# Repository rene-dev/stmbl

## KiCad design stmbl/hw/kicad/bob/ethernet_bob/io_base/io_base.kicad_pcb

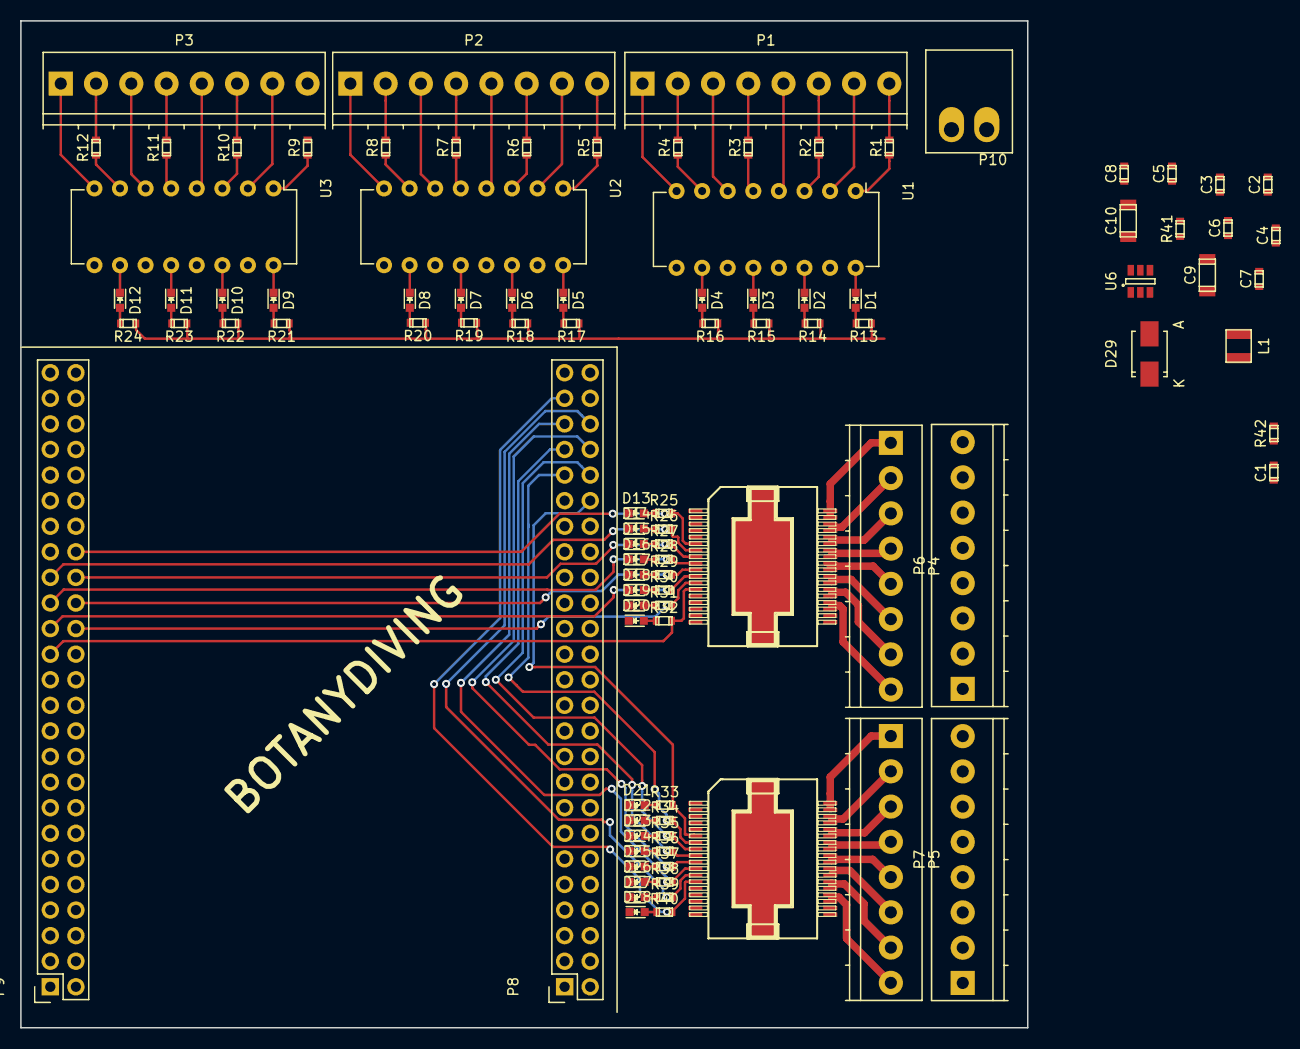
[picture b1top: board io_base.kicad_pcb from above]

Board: 2 copper layers, 99.9 x 99.9 mm, 98 parts (0 on the bottom side), 115 nets.

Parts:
C1, C2, C3, C4, C5, C6, C7, C8: 100n; C_0603
C9, C10: 10µ; C_1206
D1, D2, D3, D4, D5, D6, D7, D8, D9, D10, D11, D12, D13, D14, D15, D16, D17, D18, D19, D20, D21, D22, D23, D24, D25, D26, D27, D28: LED; LED_0603
D29: B240A; SMA_Standard
L1: 4.7µH 1.5A; SMD_INDUCTOR_32x25
P1, P2, P3, P4, P5, P6, P7: CONN_01X08; TerminalBlock_Pheonix_PT-3.5mm_8pol
P8, P9: CONN_02X25; Socket_Strip_Straight_2x25
P10: CONN_01X02; akl182-2
R1, R2, R3, R4, R5, R6, R7, R8, R9, R10, R11, R12, R13, R14, R15, R16, R17, R18, R19, R20, R21, R22, R23, R24, R25, R26, R27, R28, R29, R30, R31, R32, R33, R34, R35, R36, R37, R38, R39, R40: R; R_0603
R41: 10k; R_0603
R42: 50k; R_0603
U1, U2, U3: OPTO-TRANSISTOR-4; DIP-16_W7.62mm
U4, U5: VN808; POWERSO36
U6: ACT4088; SOT-23-6

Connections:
+3V3: P8.3, P8.4, P9.5, P9.6, P9.22, R13.1, R14.1, R15.1, R16.1, R17.1, R18.1, R19.1, R20.1, R21.1, R22.1, R23.1, R24.1
+5V: C8.1, C9.1, C10.1, L1.2, P9.3, P9.4, R42.1
+24V: C1.1, C2.1, C3.1, C4.1, C5.1, C6.1, P10.2, U4.1, U5.1, U6.2
GND: C1.2, C2.2, C3.2, C4.2, C5.2, C6.2, C8.2, C9.2, C10.2, D13.1, D14.1, D15.1, D16.1, D17.1, D18.1, D19.1, D20.1, D21.1, D22.1, D23.1, D24.1, D25.1, D26.1, D27.1, D28.1, D29.2, P6.1, P6.2, P6.3, P6.4, P6.5, P6.6, P6.7, P6.8, P7.1, P7.2, P7.3, P7.4, P7.5, P7.6, P7.7, P7.8, P8.1, P8.2, P8.5, P8.23, P8.49, P8.50, P9.1, P9.2, P9.49, P9.50, P10.1, R41.2, U1.9, U1.11, U1.13, U1.15, U2.9, U2.11, U2.13, U2.15, U3.9, U3.11, U3.13, U3.15, U4.19, U5.19, U6.5
IN1: D1.1, P9.16, U1.16
IN2: D2.1, P8.26, U1.14
IN3: D3.1, P8.25, U1.12
IN4: D4.1, P8.28, U1.10
IN5: D5.1, P8.27, U2.16
IN6: D6.1, P8.30, U2.14
IN7: D7.1, P8.29, U2.12
IN8: D8.1, P8.32, U2.10
IN9: D9.1, P8.31, U3.16
IN10: D10.1, P9.13, U3.14
IN11: D11.1, P8.33, U3.12
IN12: D12.1, P9.11, U3.10
unnamed: C7.1, U6.6
unnamed: C7.2, D29.1, L1.1, U6.1
unnamed: D1.2, R13.2
unnamed: D2.2, R14.2
unnamed: D3.2, R15.2
unnamed: D4.2, R16.2
unnamed: D5.2, R17.2
unnamed: D6.2, R18.2
unnamed: D7.2, R19.2
unnamed: D8.2, R20.2
unnamed: D9.2, R21.2
unnamed: D10.2, R22.2
unnamed: D11.2, R23.2
unnamed: D12.2, R24.2
unnamed: D13.2, R25.1
unnamed: D14.2, R26.1
unnamed: D15.2, R27.1
unnamed: D16.2, R28.1
unnamed: D17.2, R29.1
unnamed: D18.2, R30.1
unnamed: D19.2, R31.1
unnamed: D20.2, R32.1
unnamed: D21.2, R33.1
unnamed: D22.2, R34.1
unnamed: D23.2, R35.1
unnamed: D24.2, R36.1
unnamed: D25.2, R37.1
unnamed: D26.2, R38.1
unnamed: D27.2, R39.1
unnamed: D28.2, R40.1
unnamed: P1.1, U1.8
unnamed: P1.2, R4.2
unnamed: P1.3, U1.6
unnamed: P1.4, R3.2
unnamed: P1.5, U1.4
unnamed: P1.6, R2.2
unnamed: P1.7, U1.2
unnamed: P1.8, R1.2
unnamed: P2.1, U2.8
unnamed: P2.2, R8.2
unnamed: P2.3, U2.6
unnamed: P2.4, R7.2
unnamed: P2.5, U2.4
unnamed: P2.6, R6.2
unnamed: P2.7, U2.2
unnamed: P2.8, R5.2
unnamed: P3.1, U3.8
unnamed: P3.2, R12.2
unnamed: P3.3, U3.6
unnamed: P3.4, R11.2
unnamed: P3.5, U3.4
unnamed: P3.6, R10.2
unnamed: P3.7, U3.2
unnamed: P3.8, R9.2
unnamed: R1.1, U1.1
unnamed: R2.1, U1.3
unnamed: R3.1, U1.5
unnamed: R4.1, U1.7
unnamed: R5.1, U2.1
unnamed: R6.1, U2.3
unnamed: R7.1, U2.5
unnamed: R8.1, U2.7
unnamed: R9.1, U3.1
unnamed: R10.1, U3.3
unnamed: R11.1, U3.5
unnamed: R12.1, U3.7
unnamed: R41.1, R42.2, U6.4
OUT1: P9.36, R25.2, U4.6
OUT2: P9.33, R26.2, U4.7
OUT3: P9.34, R27.2, U4.8
OUT4: P9.31, R28.2, U4.9
OUT5: P9.32, R29.2, U4.10
OUT6: P9.29, R30.2, U4.11
OUT7: P9.30, R31.2, U4.12
OUT8: P9.27, R32.2, U4.13
OUT9: P8.40, R33.2, U5.6
OUT10: P8.41, R34.2, U5.7
OUT11: P8.42, R35.2, U5.8
OUT12: P8.43, R36.2, U5.9
OUT13: P8.44, R37.2, U5.10
OUT14: P8.45, R38.2, U5.11
OUT15: P8.46, R39.2, U5.12
OUT16: P8.47, R40.2, U5.13
PO1: P4.1, U4.35
PO2: P4.2, U4.33
PO3: P4.3, U4.31
PO4: P4.4, U4.29
PO5: P4.5, U4.27
PO6: P4.6, U4.25
PO7: P4.7, U4.23
PO8: P4.8, U4.21
PO9: P5.1, U5.35
PO10: P5.2, U5.33
PO11: P5.3, U5.31
PO12: P5.4, U5.29
PO13: P5.5, U5.27
PO14: P5.6, U5.25
PO15: P5.7, U5.23
PO16: P5.8, U5.21

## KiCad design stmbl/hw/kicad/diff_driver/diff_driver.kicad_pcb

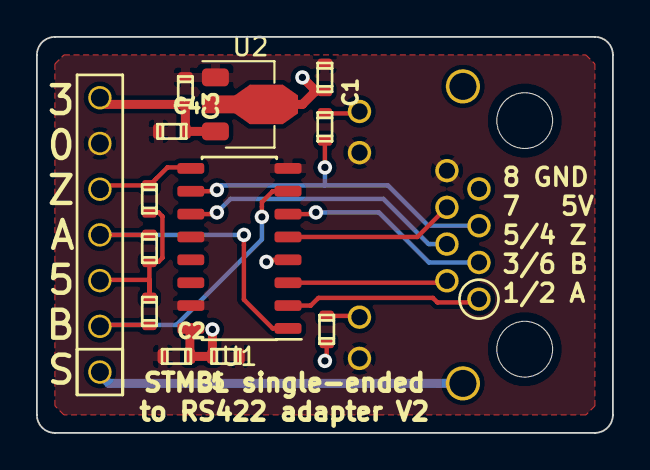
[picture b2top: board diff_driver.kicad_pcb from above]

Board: 2 copper layers, 32.0 x 22.0 mm, 14 parts (1 on the bottom side), 15 nets.

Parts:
C1, C2, C3: 100n; C_0603
C4, C5: 1n; C_0603
J1: CONN_01X07; Pin_Header_RM2.54_1x7_UP
J2: RJ45_LED
R1, R2, R3: 3.9k; R_0603
R4, R5: 560; R_0603
U1: am26ls31; SOIC-16
U2: HT75XX-1; SOT-89-3

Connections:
+3V3: C3.1, C4.1, J1.7, U2.3
+5V: C1.1, C2.1, C5.1, J1.3, J2.7, R1.1, R2.1, R3.1, R4.1, U1.4, U1.16, U2.2
A: J1.4, R1.2, U1.1
B: J1.2, R2.2, U1.7
GND: C1.2, C2.2, C3.2, C4.2, C5.2, J1.6, J2.8, J2.9, J2.11, U1.8, U1.12, U1.15, U2.1
GNDA: J1.1, J2.13
IDX: J1.5, R3.2, U1.9
unnamed: J2.1, U1.2
unnamed: J2.2, U1.3
unnamed: J2.3, U1.6
unnamed: J2.4, U1.11
unnamed: J2.5, R5.1, U1.10
unnamed: J2.6, U1.5
unnamed: J2.10, R5.2
unnamed: J2.12, R4.2

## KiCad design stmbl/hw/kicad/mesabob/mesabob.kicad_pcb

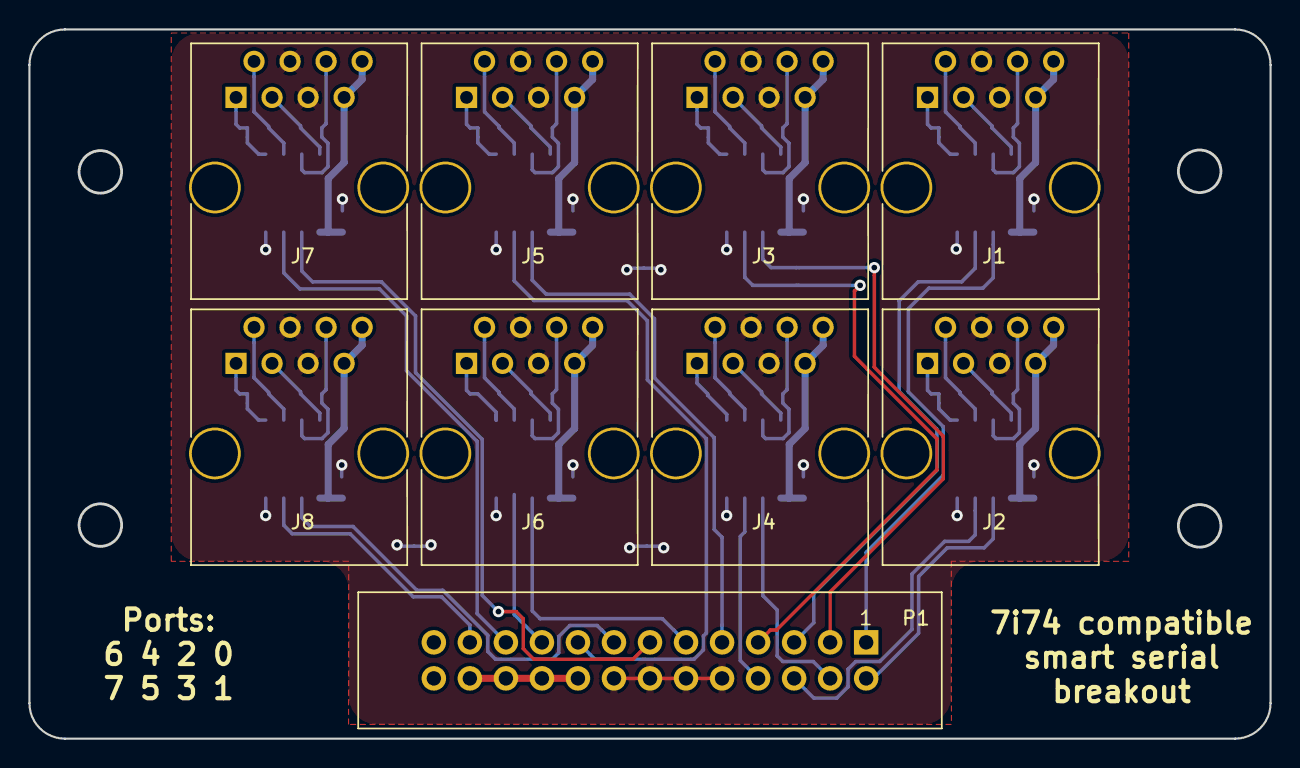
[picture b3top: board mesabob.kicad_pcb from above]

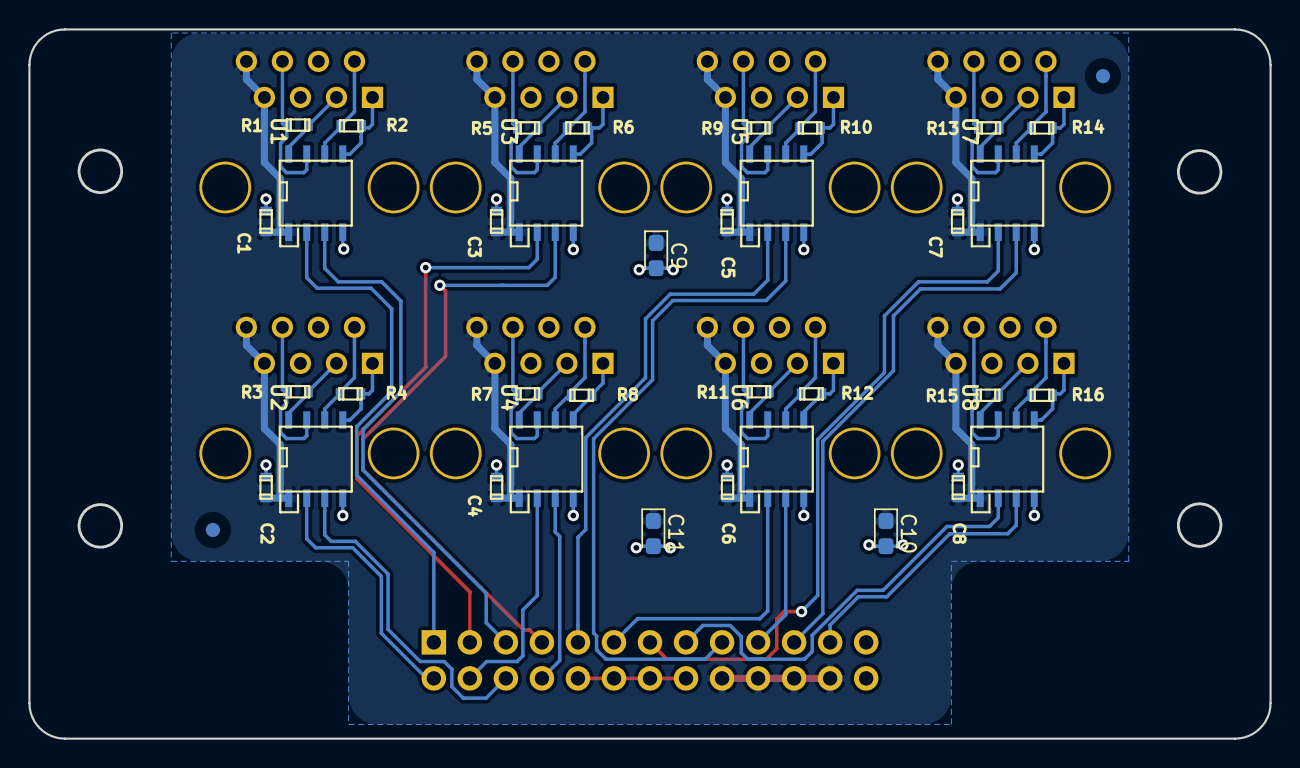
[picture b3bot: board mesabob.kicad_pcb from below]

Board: 2 copper layers, 87.5 x 50.0 mm, 44 parts (35 on the bottom side), 50 nets.

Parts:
C1, C2, C3, C4, C5, C6, C7, C8: 100n; C_0603
C9, C10, C11: CP; CP_EIA-2012-12_Kemet-R
J1, J2, J3, J4, J5, J6, J7, J8: RJ45; RJ45_8
P1: CONN_02X13; IDC_Header_Straight_26pins
R1, R2, R3, R4, R5, R6, R7, R8, R9, R10, R11, R12, R13, R14, R15, R16: R; R_0603
U1, U2, U3, U4, U5, U6, U7, U8: rs4854; SOIC-8-N

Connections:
+5V: C1.1, C2.1, C3.1, C4.1, C5.1, C6.1, C7.1, C8.1, C9.1, C10.1, C11.1, J1.7, J1.8, J2.7, J2.8, J3.7, J3.8, J4.7, J4.8, J5.7, J5.8, J6.7, J6.8, J7.7, J7.8, J8.7, J8.8, P1.18, P1.20, P1.22, P1.24, U1.1, U2.1, U3.1, U4.1, U5.1, U6.1, U7.1, U8.1
/rx0: P1.1, U1.2
/rx1: P1.2, U2.2
/rx2: P1.3, U3.2
/rx3: P1.4, U4.2
/rx4: P1.9, U5.2
/rx5: P1.11, U6.2
/rx6: P1.13, U7.2
/rx7: P1.15, U8.2
/tx0: P1.5, U1.3
/tx1: P1.6, U2.3
/tx2: P1.7, U3.3
/tx3: P1.8, U4.3
/tx4: P1.17, U5.3
/tx5: P1.19, U6.3
/tx6: P1.21, U7.3
/tx7: P1.23, U8.3
GND: C1.2, C2.2, C3.2, C4.2, C5.2, C6.2, C7.2, C8.2, C9.2, C10.2, C11.2, J1.4, J1.5, J2.4, J2.5, J3.4, J3.5, J4.4, J4.5, J5.4, J5.5, J6.4, J6.5, J7.4, J7.5, J8.4, J8.5, P1.10, P1.12, P1.14, P1.16, U1.4, U2.4, U3.4, U4.4, U5.4, U6.4, U7.4, U8.4
unnamed: J1.1, R2.1, U1.5
unnamed: J1.2, R2.2, U1.6
unnamed: J1.3, R1.2, U1.8
unnamed: J1.6, R1.1, U1.7
unnamed: J2.1, R4.1, U2.5
unnamed: J2.2, R4.2, U2.6
unnamed: J2.3, R3.2, U2.8
unnamed: J2.6, R3.1, U2.7
unnamed: J3.1, R6.1, U3.5
unnamed: J3.2, R6.2, U3.6
unnamed: J3.3, R5.2, U3.8
unnamed: J3.6, R5.1, U3.7
unnamed: J4.1, R8.1, U4.5
unnamed: J4.2, R8.2, U4.6
unnamed: J4.3, R7.2, U4.8
unnamed: J4.6, R7.1, U4.7
unnamed: J5.1, R10.1, U5.5
unnamed: J5.2, R10.2, U5.6
unnamed: J5.3, R9.2, U5.8
unnamed: J5.6, R9.1, U5.7
unnamed: J6.1, R12.1, U6.5
unnamed: J6.2, R12.2, U6.6
unnamed: J6.3, R11.2, U6.8
unnamed: J6.6, R11.1, U6.7
unnamed: J7.1, R14.1, U7.5
unnamed: J7.2, R14.2, U7.6
unnamed: J7.3, R13.2, U7.8
unnamed: J7.6, R13.1, U7.7
unnamed: J8.1, R16.1, U8.5
unnamed: J8.2, R16.2, U8.6
unnamed: J8.3, R15.2, U8.8
unnamed: J8.6, R15.1, U8.7

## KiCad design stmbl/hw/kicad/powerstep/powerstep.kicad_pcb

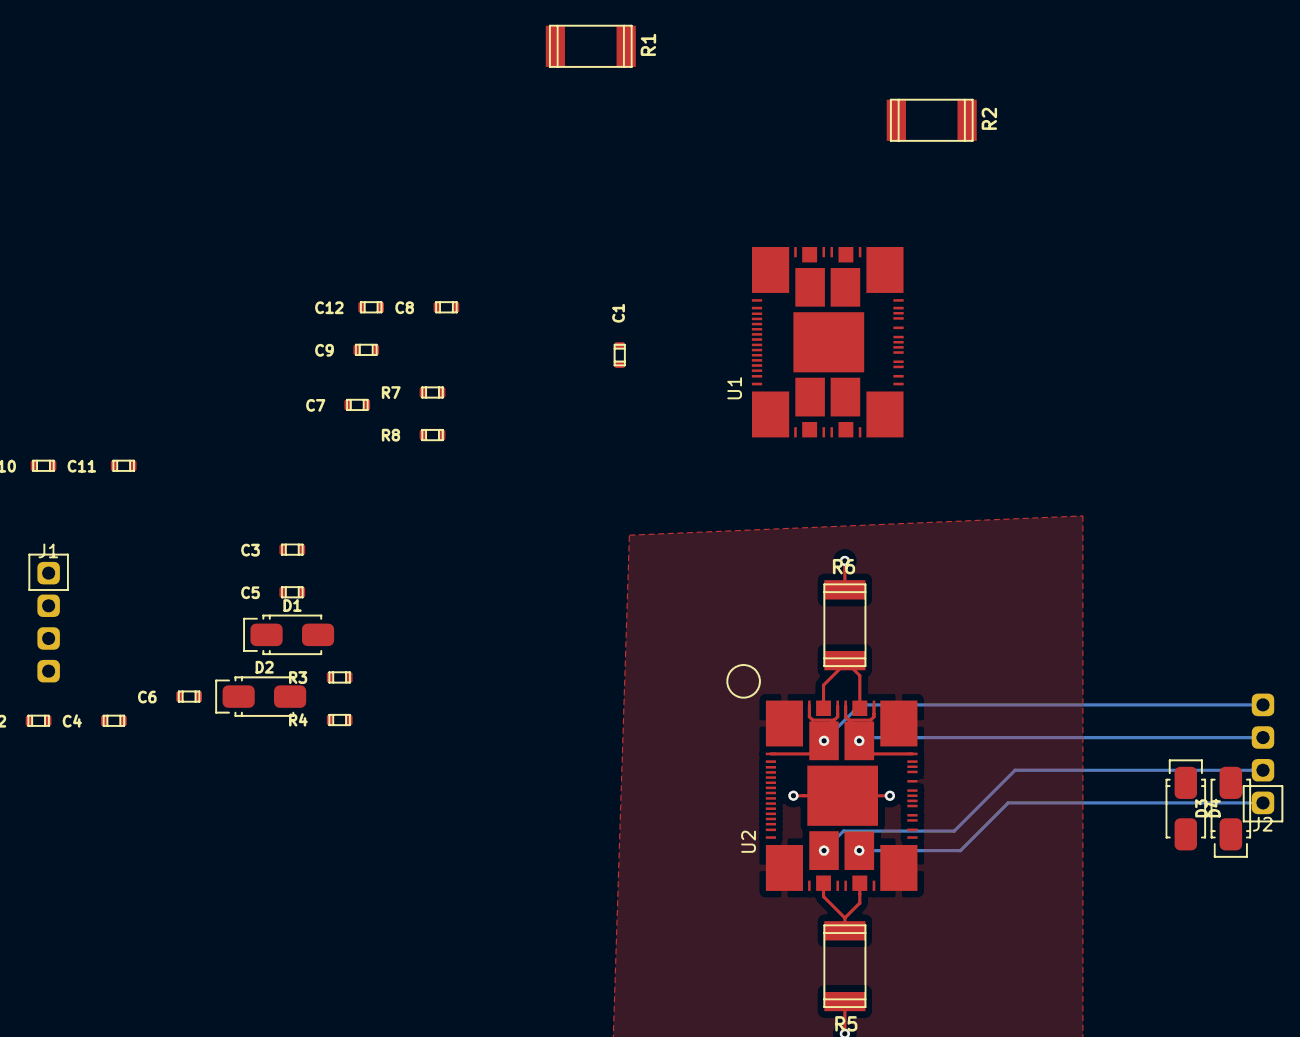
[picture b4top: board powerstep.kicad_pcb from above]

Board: 4 copper layers, 28 parts (0 on the bottom side), 31 nets.

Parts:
C1, C2, C3, C4, C5, C6, C7, C8, C9, C10, C11, C12: C; C_0603
D1, D2, D3, D4: D; SMA_Standard
J1, J2: CONN_01X04; CONN_1x04_2.54
R1, R2, R5, R6: R; R_2512
R3, R4, R7, R8: R; R_0603
U1, U2: POWERSTEP01; VFQFPNPSTEP

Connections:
/stepper2/SDI: U1.14, U2.12
/stepper/CK: U1.11, U2.11
/stepper/~CS: U1.10, U2.10
/stepper/~STBY: U1.19, U2.19
GND: C1.1, C2.1, C5.1, C6.1, C7.1, C8.1, C11.1, C12.1, R1.2, R2.2, R4.2, R5.2, R6.2, R8.2, U1.8, U2.8
unnamed: C1.2, U1.13, U1.62
unnamed: C2.2, U1.58, U1.60
unnamed: C3.1, D2.1, U1.56
unnamed: C3.2, C5.2, C6.2, D1.2, R3.1, U1.1, U1.61
unnamed: C4.1, D1.1, D2.2
unnamed: C4.2, U1.57
unnamed: C7.2, U2.13, U2.62
unnamed: C8.2, U2.58, U2.60
unnamed: C9.1, D4.1, U2.56
unnamed: C10.1, D3.1, D4.2
unnamed: C10.2, U2.57
unnamed: C9.2, C11.2, C12.2, D3.2, R7.1, U2.1, U2.61
unnamed: J1.1, U1.38
unnamed: J1.2, U1.22
unnamed: J1.3, U1.65
unnamed: J1.4, U1.7
unnamed: J2.1, U2.38
unnamed: J2.2, U2.22
unnamed: J2.3, U2.65
unnamed: J2.4, U2.7
unnamed: R1.1, U1.20, U1.34
unnamed: R2.1, U1.9, U1.77
unnamed: R3.2, R4.1, U1.54
unnamed: R5.1, U2.20, U2.34
unnamed: R6.1, U2.9, U2.77
unnamed: R7.2, R8.1, U2.54
